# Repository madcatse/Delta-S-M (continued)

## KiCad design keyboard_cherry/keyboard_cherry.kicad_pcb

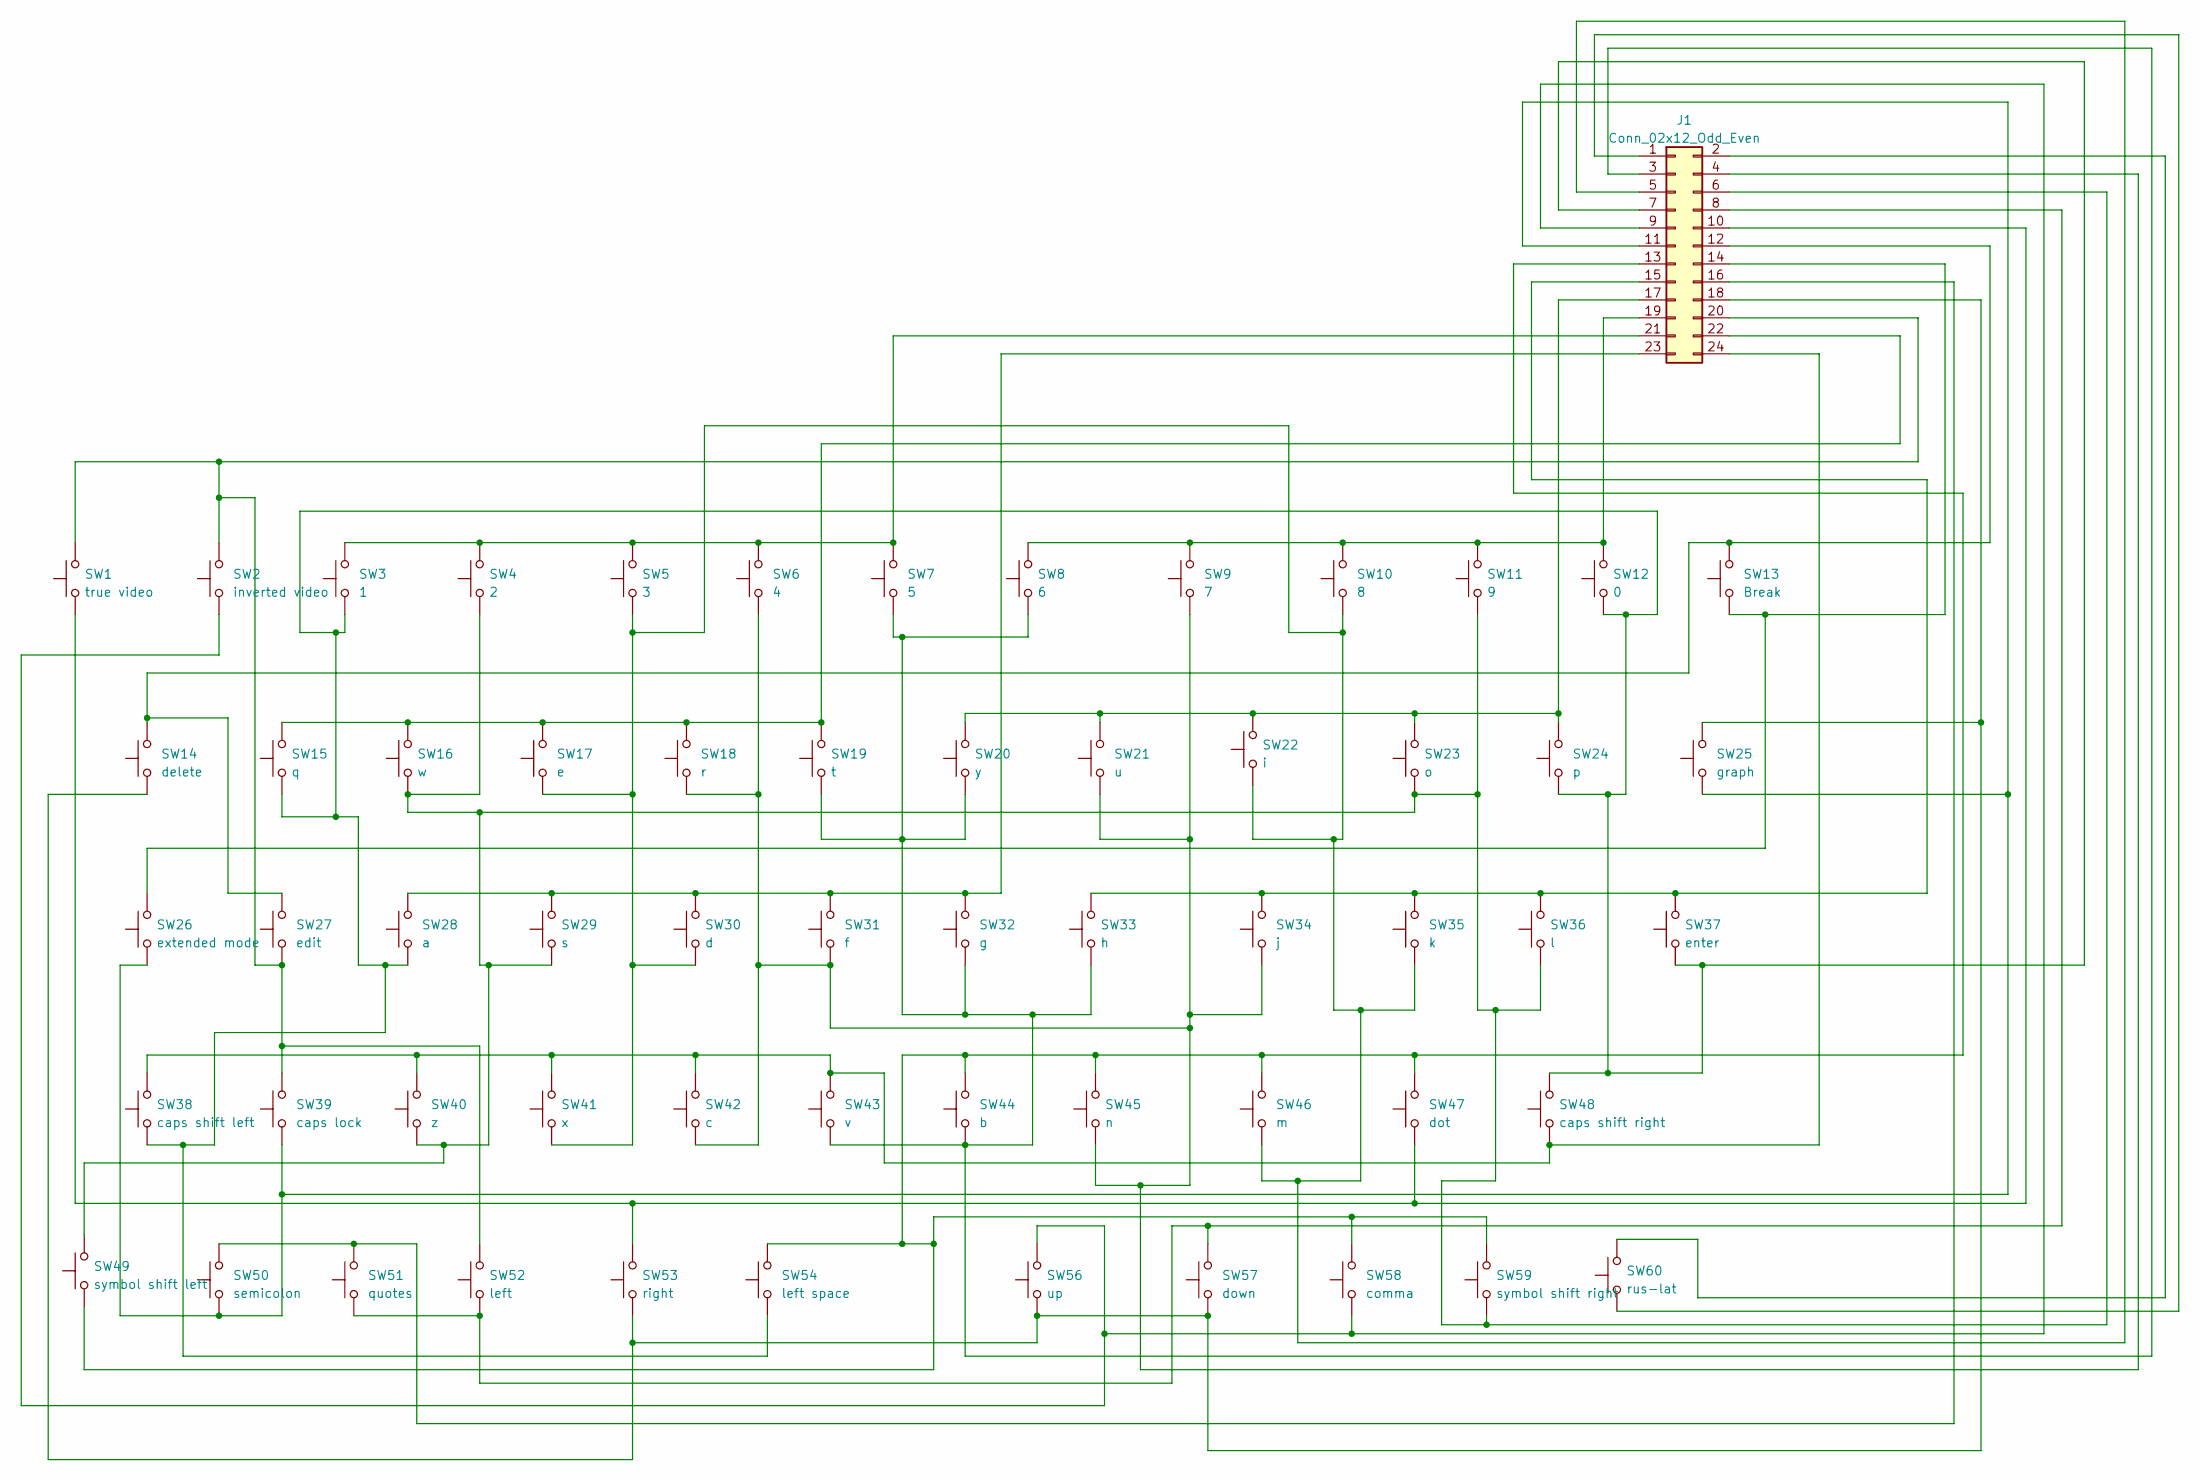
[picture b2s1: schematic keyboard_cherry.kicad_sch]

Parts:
J1: Conn_02x12_Odd_Even; IDC-Header_2x12_P2.54mm_Vertical
SW1: true video; SW_Cherry_MX_1.50u_PCB
SW2: inverted video; SW_Cherry_MX_1.50u_PCB
SW3: 1; SW_Cherry_MX_1.00u_PCB
SW4: 2; SW_Cherry_MX_1.00u_PCB
SW5: 3; SW_Cherry_MX_1.00u_PCB
SW6: 4; SW_Cherry_MX_1.00u_PCB
SW7: 5; SW_Cherry_MX_1.00u_PCB
SW8: 6; SW_Cherry_MX_1.00u_PCB
SW9: 7; SW_Cherry_MX_1.00u_PCB
SW10: 8; SW_Cherry_MX_1.00u_PCB
SW11: 9; SW_Cherry_MX_1.00u_PCB
SW12: 0; SW_Cherry_MX_1.00u_PCB
SW13: Break; SW_Cherry_MX_1.00u_PCB
SW14: delete; SW_Cherry_MX_2.00u_PCB
SW15: q; SW_Cherry_MX_1.00u_PCB
SW16: w; SW_Cherry_MX_1.00u_PCB
SW17: e; SW_Cherry_MX_1.00u_PCB
SW18: r; SW_Cherry_MX_1.00u_PCB
SW19: t; SW_Cherry_MX_1.00u_PCB
SW20: y; SW_Cherry_MX_1.00u_PCB
SW21: u; SW_Cherry_MX_1.00u_PCB
SW22: i; SW_Cherry_MX_1.00u_PCB
SW23: o; SW_Cherry_MX_1.00u_PCB
SW24: p; SW_Cherry_MX_1.00u_PCB
SW25: graph; SW_Cherry_MX_1.00u_PCB
SW26: extended mode; SW_Cherry_MX_1.75u_PCB
SW27: edit; SW_Cherry_MX_1.50u_PCB
SW28: a; SW_Cherry_MX_1.00u_PCB
SW29: s; SW_Cherry_MX_1.00u_PCB
SW30: d; SW_Cherry_MX_1.00u_PCB
SW31: f; SW_Cherry_MX_1.00u_PCB
SW32: g; SW_Cherry_MX_1.00u_PCB
SW33: h; SW_Cherry_MX_1.00u_PCB
SW34: j; SW_Cherry_MX_1.00u_PCB
SW35: k; SW_Cherry_MX_1.00u_PCB
SW36: l; SW_Cherry_MX_1.00u_PCB
SW37: enter; SW_Cherry_MX_1.75u_PCB
SW38: caps shift left; SW_Cherry_MX_2.25u_PCB
SW39: caps lock; SW_Cherry_MX_1.00u_PCB
SW40: z; SW_Cherry_MX_1.00u_PCB
SW41: x; SW_Cherry_MX_1.00u_PCB
SW42: c; SW_Cherry_MX_1.00u_PCB
SW43: v; SW_Cherry_MX_1.00u_PCB
SW44: b; SW_Cherry_MX_1.00u_PCB
SW45: n; SW_Cherry_MX_1.00u_PCB
SW46: m; SW_Cherry_MX_1.00u_PCB
SW47: dot; SW_Cherry_MX_1.00u_PCB
SW48: caps shift right; SW_Cherry_MX_2.25u_PCB
SW49: symbol shift left; SW_Cherry_MX_2.00u_PCB
SW50: semicolon; SW_Cherry_MX_1.00u_PCB
SW51: quotes; SW_Cherry_MX_1.00u_PCB
SW52: left; SW_Cherry_MX_1.00u_PCB
SW53: right; SW_Cherry_MX_1.00u_PCB
SW54: left space; SW_Cherry_MX_6.25u_PCB
SW56: up; SW_Cherry_MX_1.00u_PCB
SW57: down; SW_Cherry_MX_1.00u_PCB
SW58: comma; SW_Cherry_MX_1.00u_PCB
SW59: symbol shift right; SW_Cherry_MX_1.25u_PCB
SW60: rus-lat; SW_Cherry_MX_1.50u_PCB

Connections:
unnamed: J1.1, SW60.1
unnamed: J1.2, SW60.2
unnamed: J1.3, SW7.1, SW8.1, SW19.1, SW20.1, SW32.1, SW33.1, SW43.1, SW44.1
unnamed: J1.4, SW6.1, SW9.1, SW18.1, SW21.1, SW31.1, SW34.1, SW42.1, SW45.1
unnamed: J1.5, SW5.1, SW10.1, SW17.1, SW22.1, SW30.1, SW35.1, SW41.1, SW46.1
unnamed: J1.6, SW4.1, SW11.1, SW16.1, SW23.1, SW29.1, SW36.1, SW40.1, SW49.2, SW59.1
unnamed: J1.7, SW3.1, SW12.1, SW15.1, SW24.1, SW28.1, SW37.1, SW38.1, SW48.2, SW54.1
unnamed: J1.8, SW51.1, SW52.1, SW57.2
unnamed: J1.9, SW2.1, SW56.2, SW58.1
unnamed: J1.10, SW1.1, SW47.1, SW53.2
unnamed: J1.11, SW25.1, SW26.1, SW39.1, SW50.1
unnamed: J1.12, SW13.2, SW14.2, SW27.2
unnamed: J1.13, SW44.2, SW45.2, SW46.2, SW47.2, SW49.1, SW54.2, SW58.2, SW59.2
unnamed: J1.14, SW13.1, SW26.2
unnamed: J1.15, SW33.2, SW34.2, SW35.2, SW36.2, SW37.2
unnamed: J1.16, SW50.2, SW51.2
unnamed: J1.17, SW20.2, SW21.2, SW22.2, SW23.2, SW24.2
unnamed: J1.18, SW14.1, SW25.2, SW53.1, SW56.1, SW57.1
unnamed: J1.19, SW8.2, SW9.2, SW10.2, SW11.2, SW12.2
unnamed: J1.20, SW1.2, SW2.2, SW27.1, SW39.2, SW52.2
unnamed: J1.21, SW3.2, SW4.2, SW5.2, SW6.2, SW7.2
unnamed: J1.22, SW15.2, SW16.2, SW17.2, SW18.2, SW19.2
unnamed: J1.23, SW28.2, SW29.2, SW30.2, SW31.2, SW32.2
unnamed: J1.24, SW38.2, SW40.2, SW41.2, SW42.2, SW43.2, SW48.1

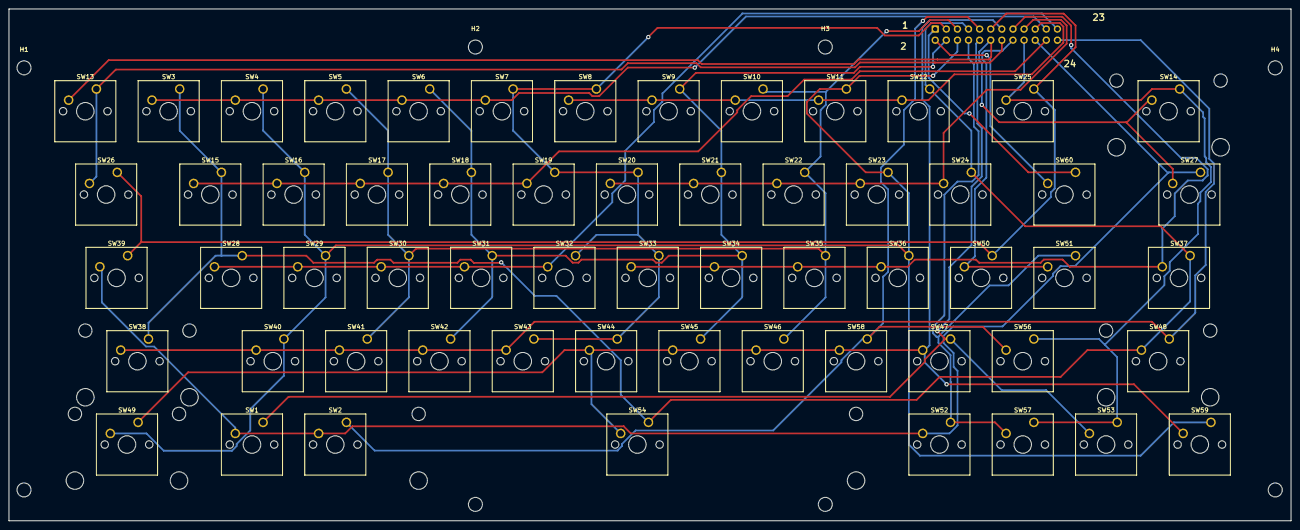
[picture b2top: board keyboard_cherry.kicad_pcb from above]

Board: 2 copper layers, 293.1 x 117.0 mm, 68 parts (1 on the bottom side), 24 nets.

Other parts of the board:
H1, H2, H3, H5, H6, H7: MountingHole_3.2mm_M3
H4, H8: MountingHole_3.2mm; MountingHole_3.2mm_M3

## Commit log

2023-03-17 Initial version
2023-03-19 20 march version
    Added 2nd list, working on the third
2023-03-21 March 21st update
2023-03-22 March 22nd additions
2023-03-22 March 22nd update 2
2023-03-22 March 22nd - 3rd edition
    List 3 is complete
2023-03-23 March 23rd Update 1
2023-03-23 March 23rd First pre-alpha
    First time ZERO errors and 93 warnings. Schematics are done, now to deal with warnings and footprints.
2023-03-23 March 24th - First Edition of PCB
2023-03-24 March 24th Second Update
2023-03-26 March 26th update
2023-03-26 March 27th Update 1
2023-03-26 March 27 Update 2
2023-03-27 SNP fix
2023-03-27 Fixes for schematics
2023-03-27 27th of March Update 1
2023-03-28 Update 28th march
2023-03-28 28th march ver2
2023-03-29 29th march 2023 Update 1
2023-03-31 March 31st Update
2023-03-31 Version 0.1 (March 31st)
2023-03-31 March 31st final update (for today)
2023-05-11 11th may update
2023-06-03 keyboard schema
2023-07-18 Small cleanup
2023-08-18 Kicad version update
2023-08-21 2108 update
2023-09-19 Added keyboard project
2023-09-19 Updade
2023-09-20 Update 20092023
2023-09-20 Late night update
2023-09-22 Roms
2023-09-23 Tracing finished
2023-09-24 24.09.23 Added test keyboard
2023-09-25 Added silkscreen to test keyboard
2023-09-25 Gerbers
2023-09-26 Keyboard fix applied (DA14 and 15)
2023-09-28 Original keyboard fix
2023-09-28 Original keyboard work
2023-09-30 Cherry Keyboard Ver0.01
2023-10-01 Keyboard_layout_final
2023-10-03 Update for U21 fix (tape loading works now)
2023-10-08 Version 1.0 schematics and PCB complete
2023-10-09 Gerbers and Version 1.0 fix
2023-10-09 Keyboard models update
2023-10-10 Update 3d models for keyboard and capacitor
2023-10-10 Full_keys
2023-10-11 3d model fix
2023-10-12 3d models update
2023-10-14 Adding plate to keyboard
2023-10-16 Update 16.10.2023 (3D stuff)
2023-10-19 Keyboard gerbers and 3d modelling of top case
2023-10-20 Added 4th hole for support, changed diameter to M3
2023-10-21 3d Models finish
2023-10-22 3d models fix
2023-11-10 Small silkscreen fix
2023-11-13 Keyboard rev1 raw data
2023-11-13 Keyboard Rev.2 Layout Added
2023-11-13 DXF panel
2023-11-13 Rev2 Update
2023-11-13 Layout
2023-11-13 Routing rev2
2023-11-13 Cleanup
2023-11-13 Layout ver.2 finalised
2023-11-13 3d design for ver2 final
2023-11-18 Clearing DOCs folder
2023-12-16 Video connector fix and labels
2024-02-01 Gerbers refresh
2024-02-06 Fixing a silly keyboard layout error
2024-02-26 Update 3d models
2024-03-08 Typo error fix (, and .)
2024-03-18 Version 1.2 update
2024-03-18 Hyperlynx files
2024-03-18 Update 1.2, additional pins
2024-03-18 Topology for version 1.2
2024-03-20 Gerbers update
2024-03-21 Documentation for 1.2
2024-04-02 Fixes
2024-04-04 Gerbers 05042024
2024-04-08 Gerbers 08042024
2024-12-28 Roms upload
2025-02-26 Update files
2025-03-24 Kicad 9 Update
2026-05-25 Clean up
